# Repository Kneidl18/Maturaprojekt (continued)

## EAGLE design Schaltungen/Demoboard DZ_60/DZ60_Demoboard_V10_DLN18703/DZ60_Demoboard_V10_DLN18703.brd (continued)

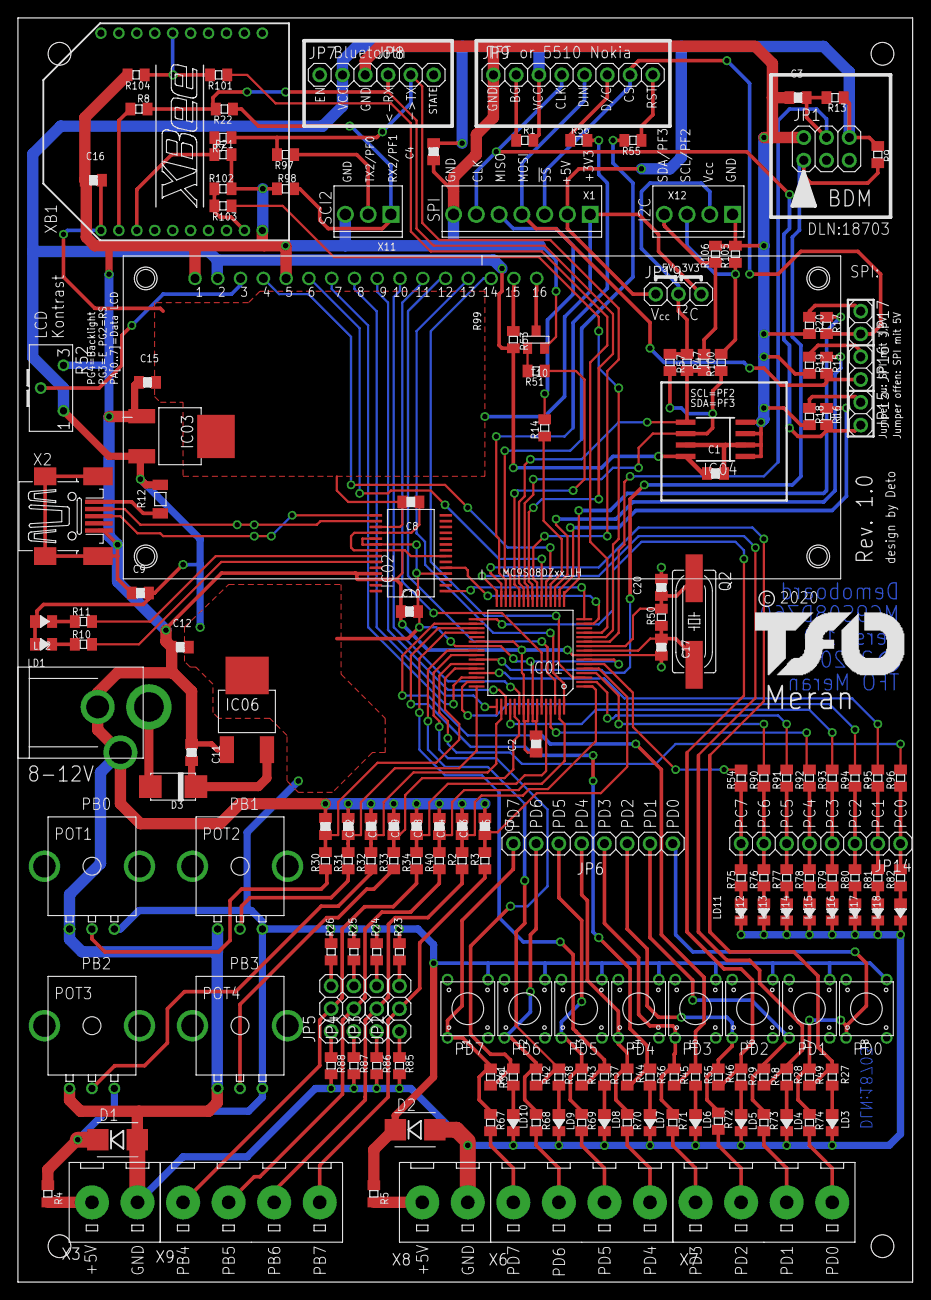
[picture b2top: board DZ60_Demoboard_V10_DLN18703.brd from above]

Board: 2 copper layers, 99.8 x 141.0 mm, 180 parts (0 on the bottom side), 146 nets.

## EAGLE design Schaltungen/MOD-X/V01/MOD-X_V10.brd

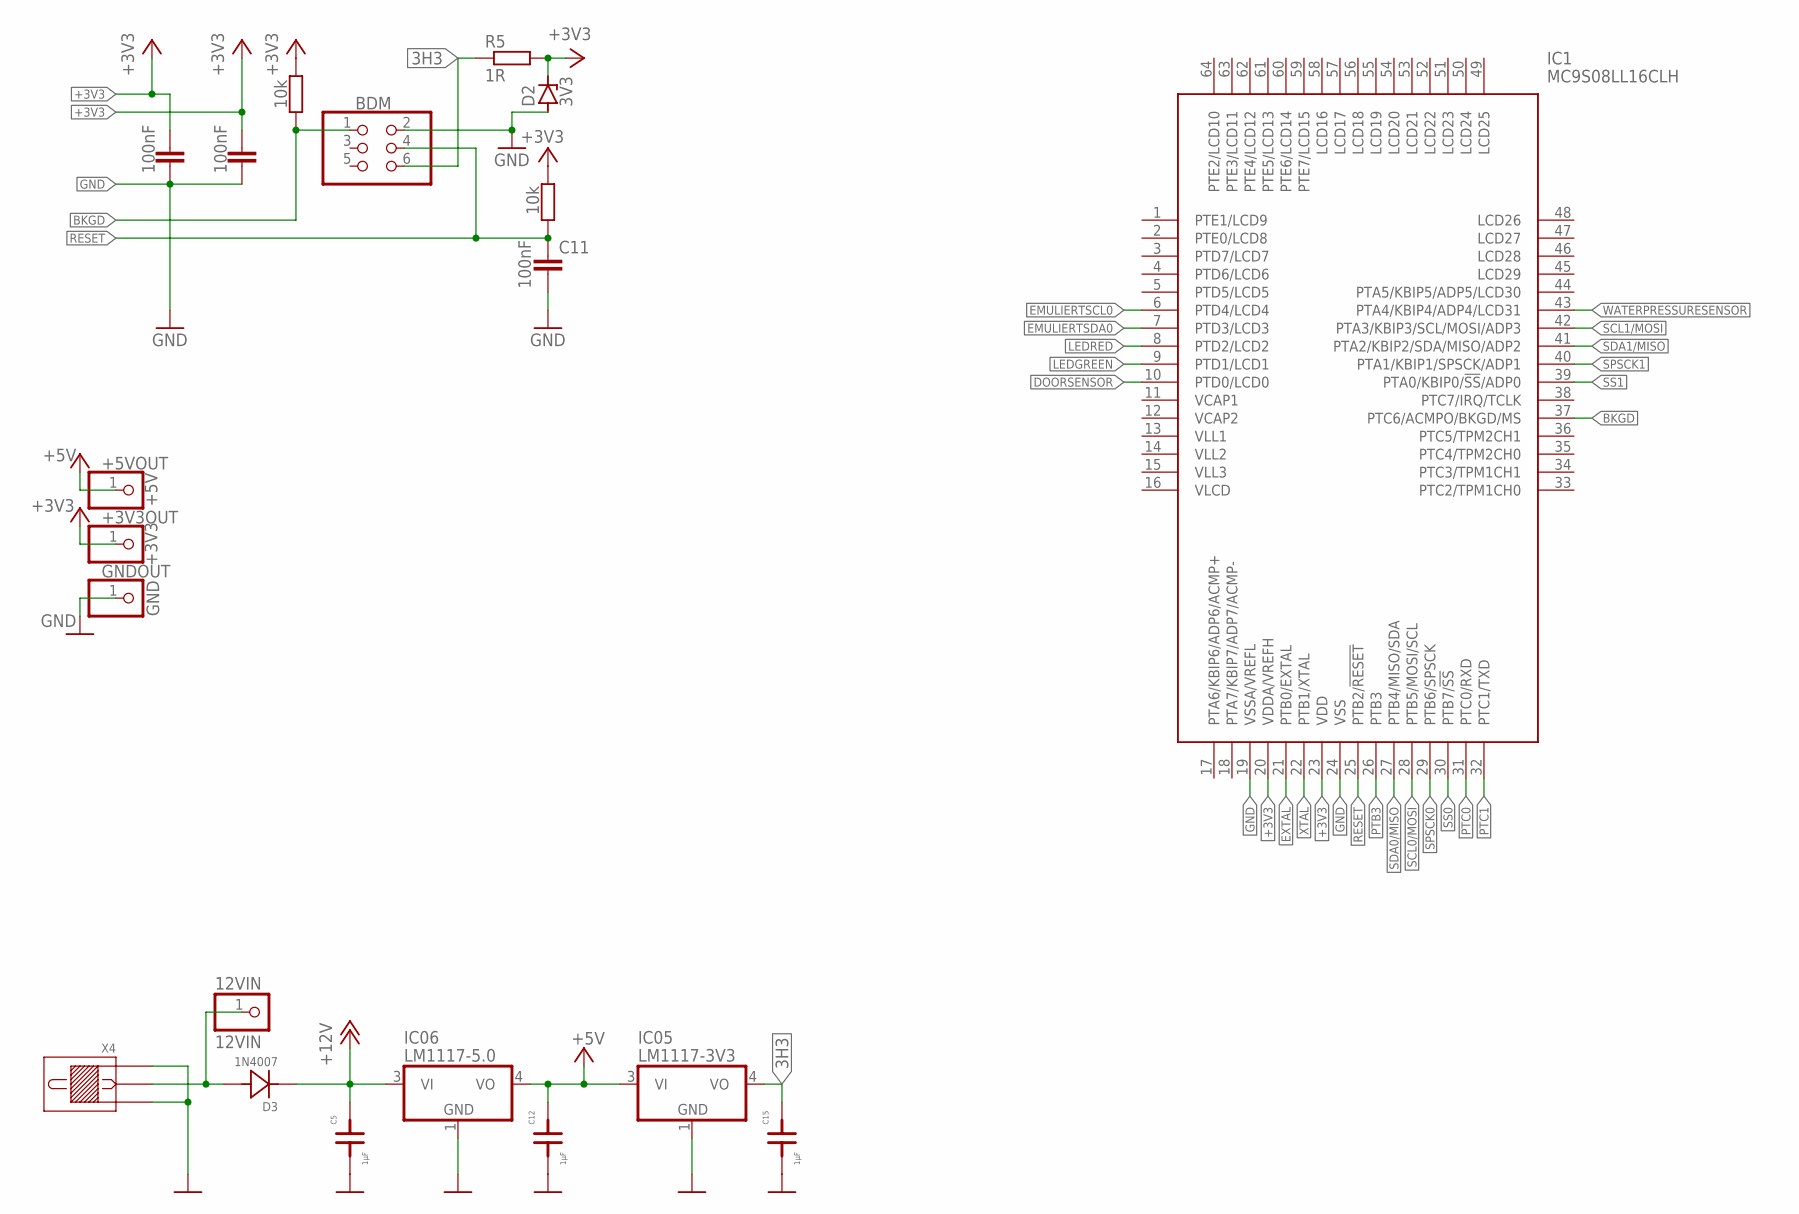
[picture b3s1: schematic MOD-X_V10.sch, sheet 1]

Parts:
12VIN: 12VIN; 1X01
+3V3OUT: +3V3; 1X01
+5VOUT: +5V; 1X01
BDM: PINHD-2X3; 2X03
C5, C12, C15: 1µF; 0805F
C9, C10, C11: 100nF; C0805
D2: 3V3; SOD80C
D3: 1N4007; MELF_B
GNDOUT: GND; 1X01
IC1: MC9S08LL16CLH; QFP50P1200X1200X160-64N
IC05: LM1117-3V3; DPAK
IC06: LM1117-5.0; DPAK
R5: 1R; R0805
R16, R17: 10k; R0805
X4: SPP

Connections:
3H3: BDM.6, C15.2, IC05.4 (VO), R5.1
+3V3: +3V3OUT.1, C9.1, C10.1, D2.C, IC1.20 (VDDA/VREFH), IC1.23 (VDD), R5.2, R16.2, R17.2; also elsewhere on the board
+5V: +5VOUT.1, C12.2, IC05.3 (VI), IC06.4 (VO); also elsewhere on the board
+12V: C5.2, D3.K, IC06.3 (VI); also elsewhere on the board
BKGD: BDM.1, IC1.37 (PTC6/ACMPO/BKGD/MS), R16.1
DOORSENSOR: IC1.10 (PTD0/LCD0); also elsewhere on the board
EMULIERTSCL0: IC1.6 (PTD4/LCD4); also elsewhere on the board
EMULIERTSDA0: IC1.7 (PTD3/LCD3); also elsewhere on the board
EXTAL: IC1.21 (PTB0/EXTAL); also elsewhere on the board
GND: BDM.2, C5.1, C9.2, C10.2, C11.2, C12.1, C15.1, D2.A, GNDOUT.1, IC1.19 (VSSA/VREFL), IC1.24 (VSS), IC05.1 (GND), IC06.1 (GND), X4.1, X4.3; also elsewhere on the board
LEDGREEN: IC1.9 (PTD1/LCD1); also elsewhere on the board
LEDRED: IC1.8 (PTD2/LCD2); also elsewhere on the board
unnamed: 12VIN.1, D3.A, X4.2
PTB3: IC1.26 (PTB3); also elsewhere on the board
PTC0: IC1.31 (PTC0/RXD); also elsewhere on the board
PTC1: IC1.32 (PTC1/TXD); also elsewhere on the board
RESET: BDM.4, C11.1, IC1.25 (PTB2/!RESET), R17.1
SCL0/MOSI: IC1.28 (PTB5/MOSI/SCL); also elsewhere on the board
SCL1/MOSI: IC1.42 (PTA3/KBIP3/SCL/MOSI/ADP3)
SDA0/MISO: IC1.27 (PTB4/MISO/SDA); also elsewhere on the board
SDA1/MISO: IC1.41 (PTA2/KBIP2/SDA/MISO/ADP2)
SPSCK0: IC1.29 (PTB6/SPSCK); also elsewhere on the board
SPSCK1: IC1.40 (PTA1/KBIP1/SPSCK/ADP1)
SS0: IC1.30 (PTB7/!SS); also elsewhere on the board
SS1: IC1.39 (PTA0/KBIP0/!SS!/ADP0)
WATERPRESSURESENSOR: IC1.43 (PTA4/KBIP4/ADP4/LCD31); also elsewhere on the board
XTAL: IC1.22 (PTB1/XTAL); also elsewhere on the board

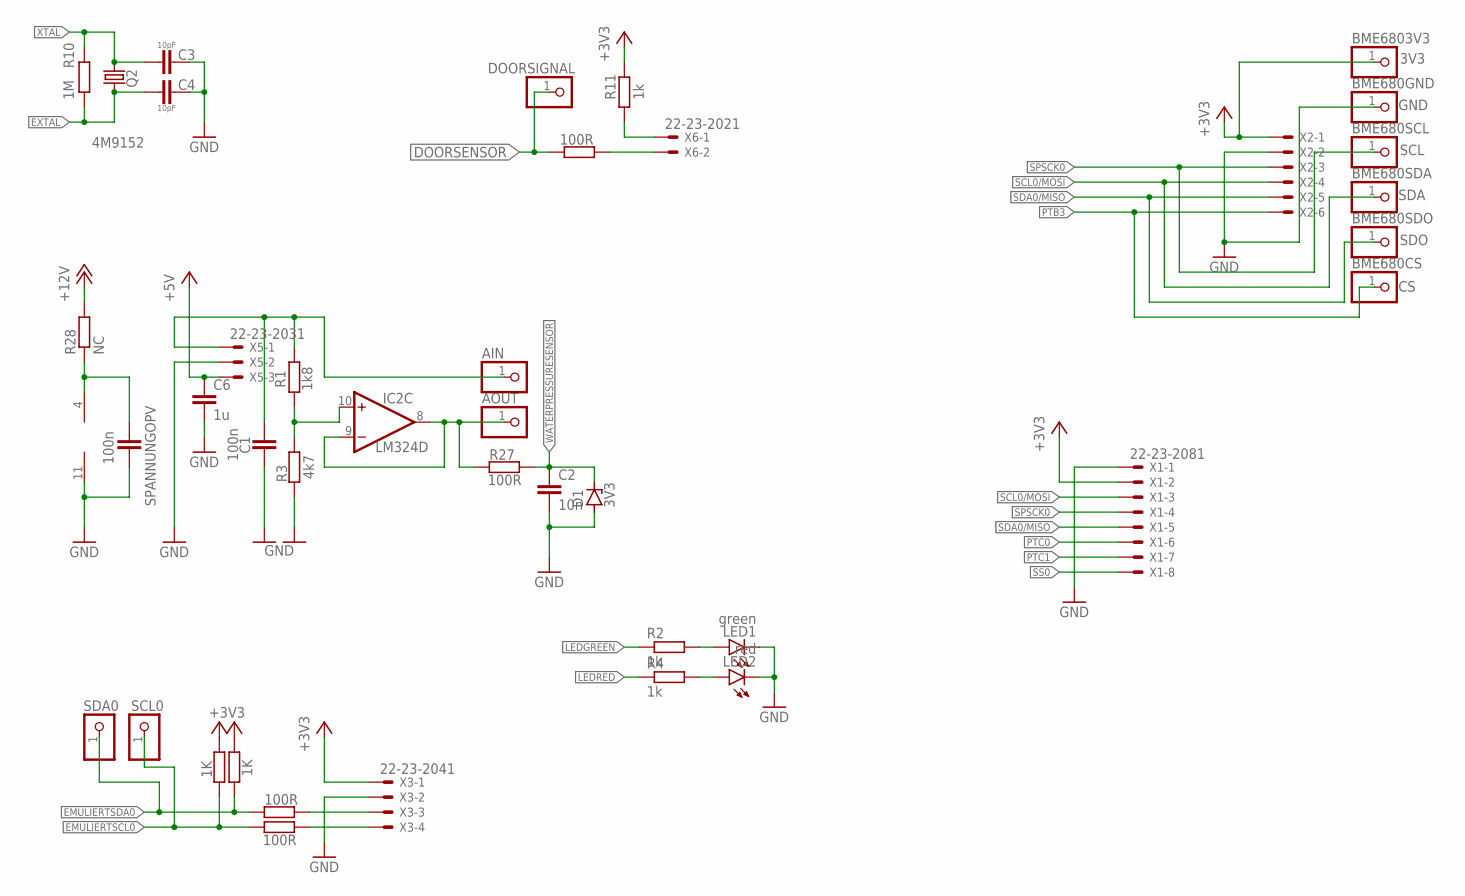
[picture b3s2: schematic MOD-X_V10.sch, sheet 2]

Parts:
AIN: PINHD-1X1; 1X01
AOUT: PINHD-1X1; 1X01
BME680CS: CS; 1X01
BME680GND: GND; 1X01
BME680SCL: SCL; 1X01
BME680SDA: SDA; 1X01
BME680SDO: SDO; 1X01
BME6803V3: 3V3; 1X01
C1: 100n; C0805
C2: 10n; C0805
C3, C4: 10pF; C0805
C6: 1u; C0805
D1: 3V3; SOD80C
DOORSIGNAL: PINHD-1X1; 1X01
IC2: LM324D; SO14
LED1: green; CHIP-LED0805
LED2: red; CHIP-LED0805
Q2: 4M9152; HC49UP
R1: 1k8; R0805
R2, R4, R11: 1k; R0805
R3: 4k7; R0805
R6, R7, R8, R27: 100R; R0805
R9, R18: 1K; R0805
R10: 1M; R0805
R28: NC; R0805
SCL0: PINHD-1X1; 1X01
SDA0: PINHD-1X1; 1X01
SPANNUNGOPV: 100n; C0805
X1: 22-23-2081
X2: 22-23-2061
X3: 22-23-2041
X5: 22-23-2031
X6: 22-23-2021

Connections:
+3V3: BME6803V3.1, R9.2, R11.2, R18.2, X1.2, X2.1, X3.1; also elsewhere on the board
+5V: C6.1, X5.3; also elsewhere on the board
+12V: R28.2; also elsewhere on the board
DOORSENSOR: DOORSIGNAL.1, R6.1; also elsewhere on the board
EMULIERTSCL0: R8.1, R18.1, SCL0.1; also elsewhere on the board
EMULIERTSDA0: R7.1, R9.1, SDA0.1; also elsewhere on the board
EXTAL: C4.1, Q2.1, R10.1; also elsewhere on the board
GND: BME680GND.1, C1.2, C2.2, C3.2, C4.2, C6.2, D1.A, IC2.11 (V-), LED1.C, LED2.C, R3.1, SPANNUNGOPV.2, X1.1, X2.2, X3.2, X5.2; also elsewhere on the board
LEDGREEN: R2.1; also elsewhere on the board
LEDRED: R4.1; also elsewhere on the board
unnamed: IC2.10 (+IN), R1.1, R3.2
unnamed: AIN.1, C1.1, R1.2, X5.1
unnamed: R6.2, X6.2
unnamed: R11.1, X6.1
unnamed: IC2.4 (V+), R28.1, SPANNUNGOPV.1
unnamed: LED1.A, R2.2
unnamed: R8.2, X3.4
unnamed: R7.2, X3.3
unnamed: LED2.A, R4.2
unnamed: AOUT.1, IC2.8 (OUT), IC2.9 (-IN), R27.1
PTB3: BME680CS.1, X2.6; also elsewhere on the board
PTC0: X1.6; also elsewhere on the board
PTC1: X1.7; also elsewhere on the board
SCL0/MOSI: BME680SDA.1, X1.3, X2.4; also elsewhere on the board
SDA0/MISO: BME680SDO.1, X1.5, X2.5; also elsewhere on the board
SPSCK0: BME680SCL.1, X1.4, X2.3; also elsewhere on the board
SS0: X1.8; also elsewhere on the board
WATERPRESSURESENSOR: C2.1, D1.C, R27.2; also elsewhere on the board
XTAL: C3.1, Q2.2, R10.2; also elsewhere on the board

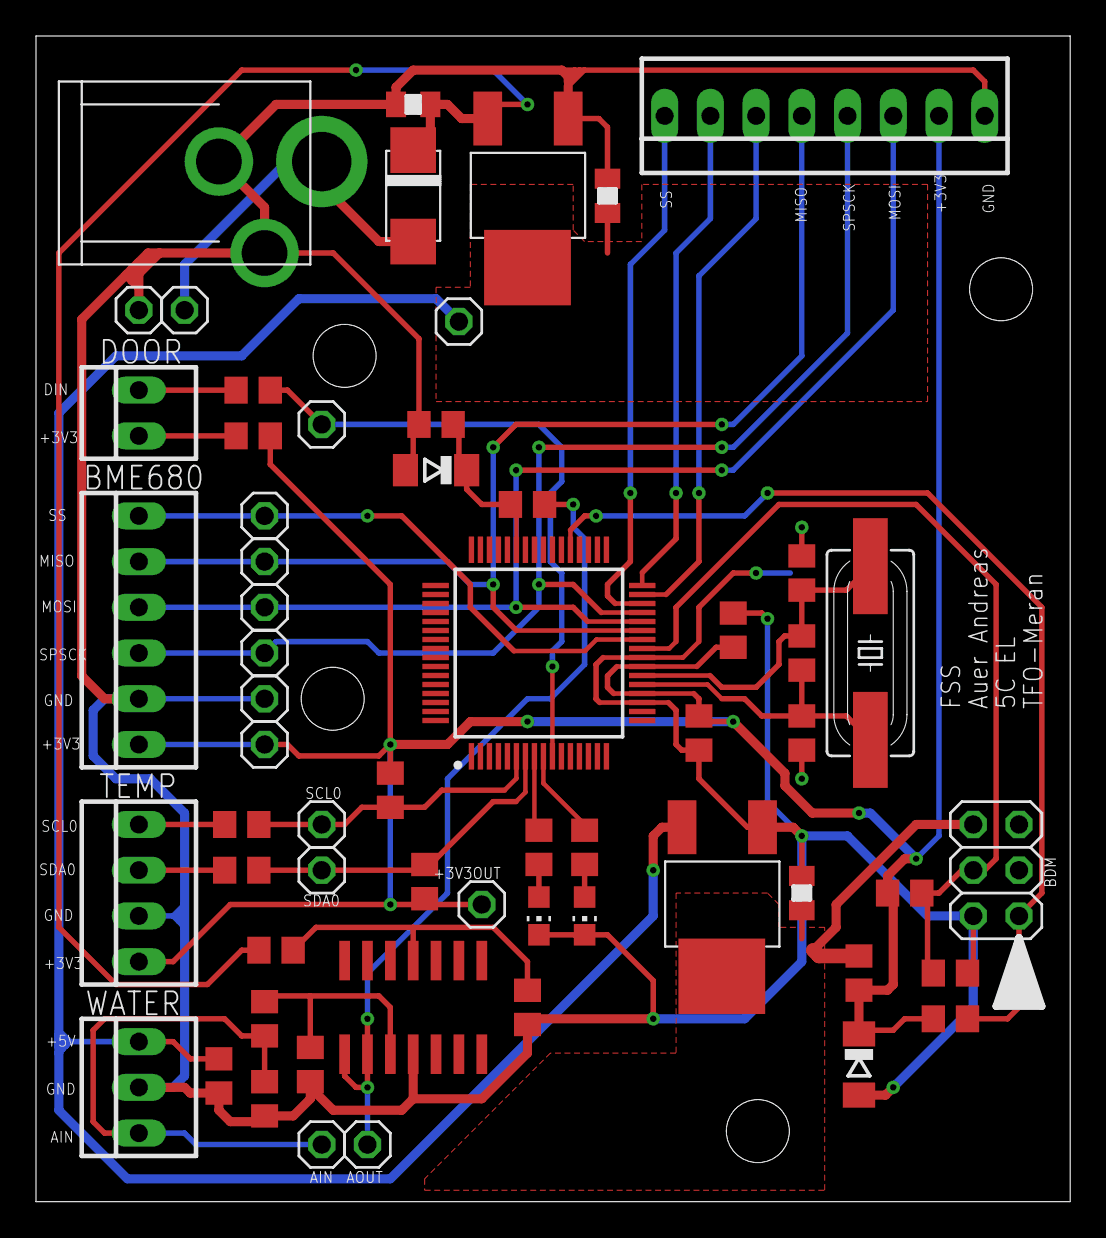
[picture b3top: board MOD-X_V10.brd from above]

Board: 2 copper layers, 57.5 x 64.8 mm, 60 parts (0 on the bottom side), 33 nets.

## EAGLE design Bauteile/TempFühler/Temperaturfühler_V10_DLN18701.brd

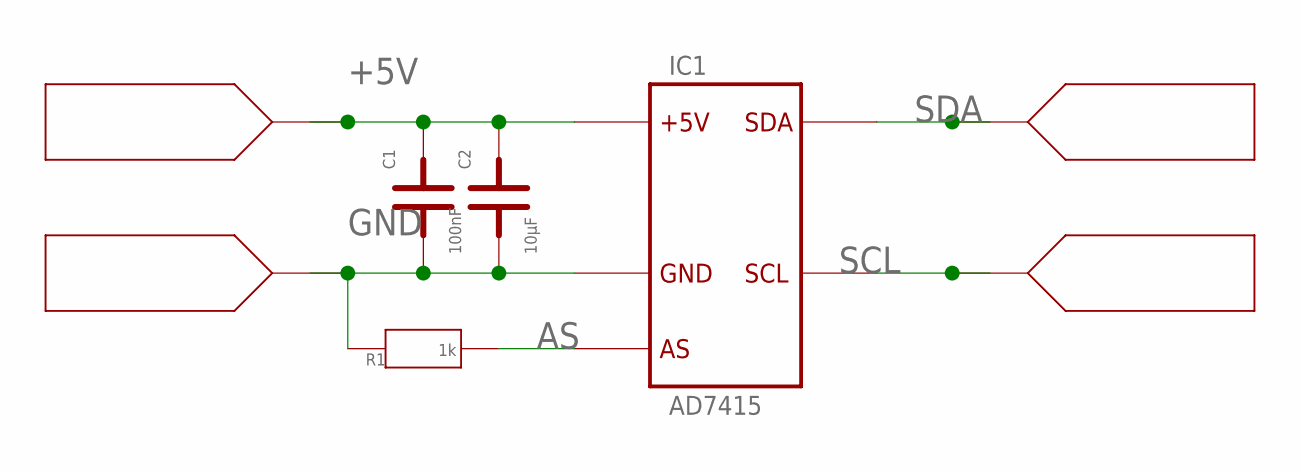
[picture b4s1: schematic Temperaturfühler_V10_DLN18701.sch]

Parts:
C1: 100nF; 0805F
C2: 10µF; 0805F
IC1: AD7415; SOT23-5L
LP1, LP2, LP3, LP4: LP1; LPS1
R1: 1k; 0805

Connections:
+5V: C1.2, C2.2, IC1.3 (+5V), LP3.1
AS: IC1.1 (AS), R1.1
GND: C1.1, C2.1, IC1.2 (GND), LP4.1, R1.2
SCL: IC1.4 (SCL), LP2.1
SDA: IC1.5 (SDA), LP1.1

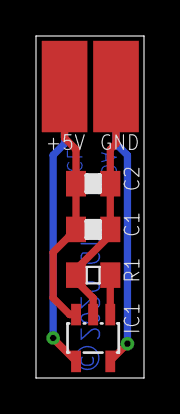
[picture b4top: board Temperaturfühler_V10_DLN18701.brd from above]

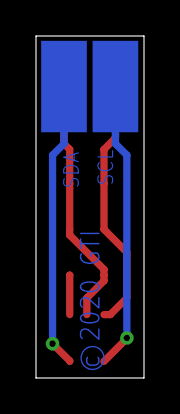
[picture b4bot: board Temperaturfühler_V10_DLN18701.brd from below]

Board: 2 copper layers, 6.0 x 19.0 mm, 8 parts (2 on the bottom side), 5 nets.

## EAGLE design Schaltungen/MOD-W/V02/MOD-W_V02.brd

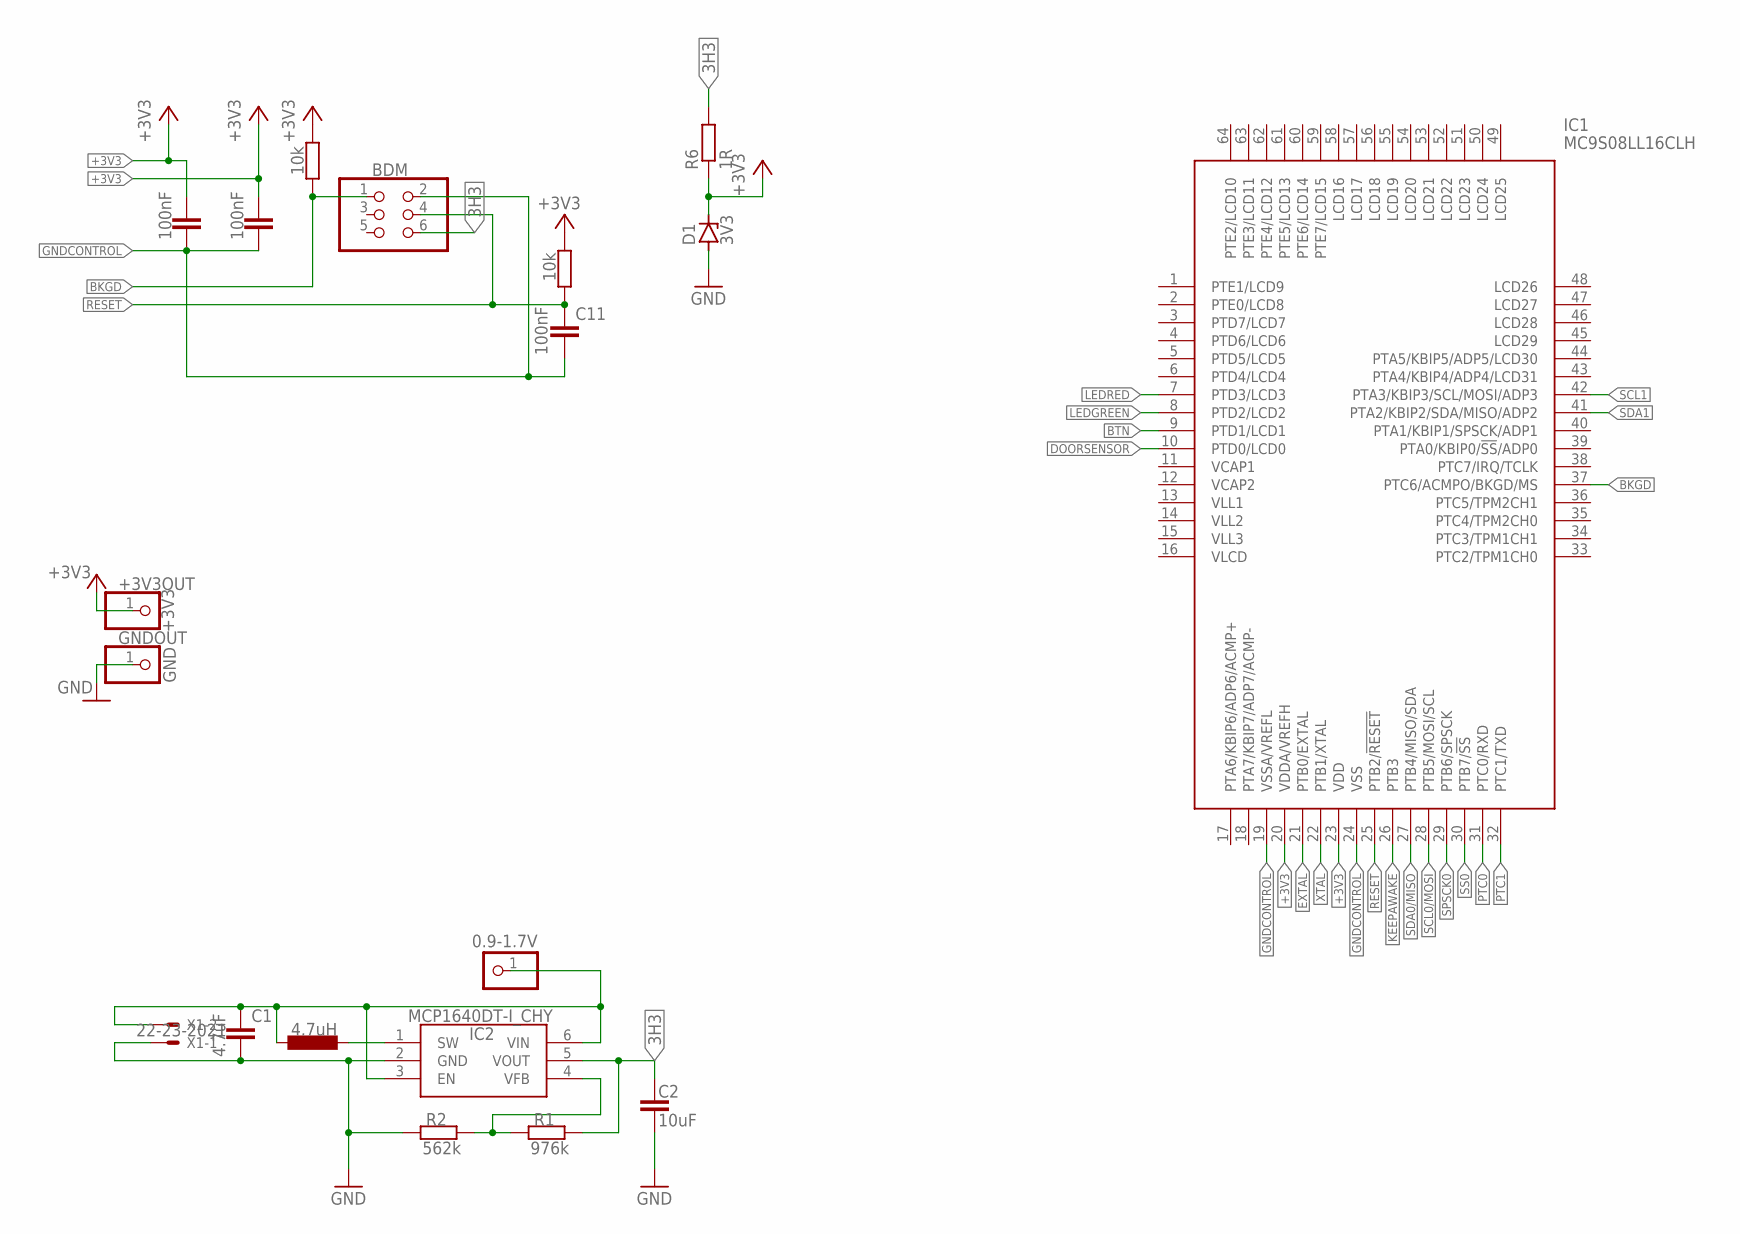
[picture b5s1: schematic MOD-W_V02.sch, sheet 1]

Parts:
+3V3OUT: +3V3; 1X01
BAT: 0.9-1.7V; 1X01
BDM: PINHD-2X3; 2X03
C1: 4.7uF; C0805
C2: 10uF; C0805
C9, C10, C11: 100nF; C0805
D1: 3V3; SOD80C
GNDOUT: GND; 1X01
IC1: MC9S08LL16CLH; QFP50P1200X1200X160-64N
IC2: MCP1640DT-I_CHY; SOT95P270X145-6N
L1: 4.7uH; L2012C
R1: 976k; R0805
R2: 562k; R0805
R6: 1R; R0805
R16, R17: 10k; R0805
X1: 22-23-2021

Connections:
3H3: BDM.6, C2.1, IC2.5 (VOUT), R1.2, R6.2
+3V3: +3V3OUT.1, C9.1, C10.1, D1.C, IC1.20 (VDDA/VREFH), IC1.23 (VDD), R6.1, R16.2, R17.2; also elsewhere on the board
BKGD: BDM.1, IC1.37 (PTC6/ACMPO/BKGD/MS), R16.1
BTN: IC1.9 (PTD1/LCD1)
DOORSENSOR: IC1.10 (PTD0/LCD0); also elsewhere on the board
EXTAL: IC1.21 (PTB0/EXTAL); also elsewhere on the board
GND: C1.2, C2.2, D1.A, GNDOUT.1, IC2.2 (GND), R2.1, X1.1; also elsewhere on the board
GNDCONTROL: BDM.2, C9.2, C10.2, C11.2, IC1.19 (VSSA/VREFL), IC1.24 (VSS); also elsewhere on the board
KEEPAWAKE: IC1.26 (PTB3); also elsewhere on the board
LEDGREEN: IC1.8 (PTD2/LCD2); also elsewhere on the board
LEDRED: IC1.7 (PTD3/LCD3); also elsewhere on the board
unnamed: BAT.1, C1.1, IC2.3 (EN), IC2.6 (VIN), L1.2, X1.2
unnamed: IC2.4 (VFB), R1.1, R2.2
unnamed: IC2.1 (SW), L1.1
PTC0: IC1.31 (PTC0/RXD); also elsewhere on the board
PTC1: IC1.32 (PTC1/TXD); also elsewhere on the board
RESET: BDM.4, C11.1, IC1.25 (PTB2/!RESET), R17.1
SCL0/MOSI: IC1.28 (PTB5/MOSI/SCL); also elsewhere on the board
SCL1: IC1.42 (PTA3/KBIP3/SCL/MOSI/ADP3); also elsewhere on the board
SDA0/MISO: IC1.27 (PTB4/MISO/SDA); also elsewhere on the board
SDA1: IC1.41 (PTA2/KBIP2/SDA/MISO/ADP2); also elsewhere on the board
SPSCK0: IC1.29 (PTB6/SPSCK); also elsewhere on the board
SS0: IC1.30 (PTB7/!SS); also elsewhere on the board
XTAL: IC1.22 (PTB1/XTAL); also elsewhere on the board

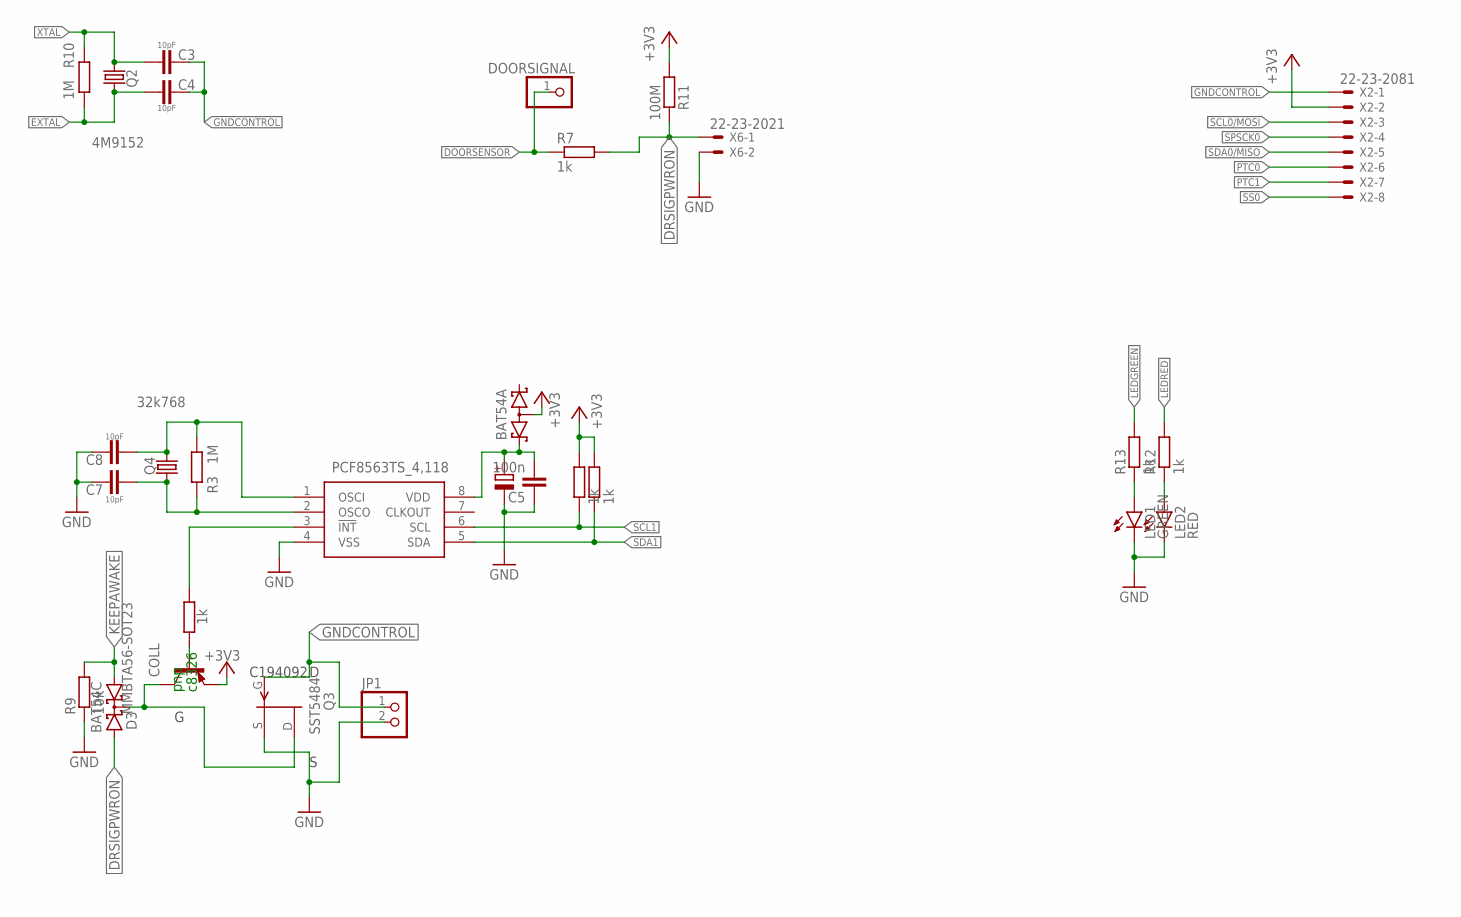
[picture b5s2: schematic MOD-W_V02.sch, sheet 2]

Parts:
C3, C4, C7, C8: 10pF; C0805
C5: 100n; C0805
C6: 100u; PANASONIC_E
D2: BAT54A; SOT23
D3: BAT54C; SOT23
DOORSIGNAL: PINHD-1X1; 1X01
IC3: PCF8563TS_4,118; SOP65P490X110-8N
JP1: PINHD-1X2; 1X02
LED1: GREEN; CHIP-LED0805
LED2: RED; CHIP-LED0805
Q1: MMBTA56-SOT23; SOT23
Q2: 4M9152; HC49UP
Q3: SST5484; SOT23
Q4: 32k768; TC38H
R3, R10: 1M; R0805
R4, R5, R7, R8, R12, R13: 1k; R0805
R9: 10k; R0805
R11: 100M; R0805
X2: 22-23-2081
X6: 22-23-2021

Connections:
+3V3: D2.3 (AA), Q1.2 (E), R4.2, R5.2, R11.1, X2.2; also elsewhere on the board
COLL: D3.3 (CC), Q1.3 (C), Q3.1 (D)
DOORSENSOR: DOORSIGNAL.1, R7.1; also elsewhere on the board
DRSIGPWRON: D3.2 (A2), R7.2, R11.2, X6.1
EXTAL: C4.1, Q2.1, R10.1; also elsewhere on the board
EXTAL1: C8.1, IC3.1 (OSCI), Q4.1, R3.1
GND: C5.1, C6.-, C7.2, C8.2, IC3.4 (VSS), JP1.2, LED1.C, LED2.C, Q3.2 (S), R9.1, X6.2; also elsewhere on the board
GNDCONTROL: C3.2, C4.2, JP1.1, Q3.3 (G), X2.1; also elsewhere on the board
KEEPAWAKE: D3.1 (A1), R9.2; also elsewhere on the board
LEDGREEN: R13.2; also elsewhere on the board
LEDRED: R12.2; also elsewhere on the board
unnamed: IC3.3 (!INT), R8.2
unnamed: LED1.A, R13.1
unnamed: LED2.A, R12.1
unnamed: Q1.1 (B), R8.1
unnamed: C5.2, C6.+, D2.2 (K2), IC3.8 (VDD)
PTC0: X2.6; also elsewhere on the board
PTC1: X2.7; also elsewhere on the board
SCL0/MOSI: X2.3; also elsewhere on the board
SCL1: IC3.6 (SCL), R4.1; also elsewhere on the board
SDA0/MISO: X2.5; also elsewhere on the board
SDA1: IC3.5 (SDA), R5.1; also elsewhere on the board
SPSCK0: X2.4; also elsewhere on the board
SS0: X2.8; also elsewhere on the board
XTAL: C3.1, Q2.2, R10.2; also elsewhere on the board
XTAL1: C7.1, IC3.2 (OSCO), Q4.2, R3.2

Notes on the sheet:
c8326
pnp
C194092

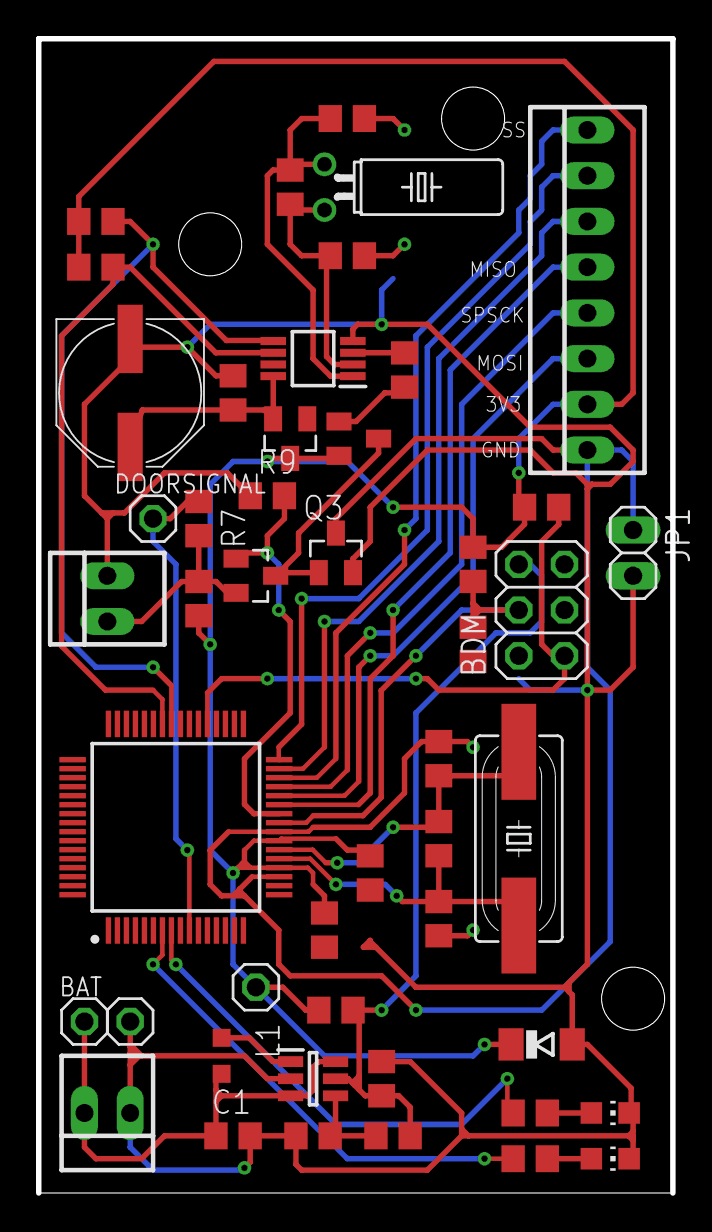
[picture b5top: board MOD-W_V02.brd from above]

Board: 2 copper layers, 35.2 x 64.1 mm, 48 parts (0 on the bottom side), 32 nets.

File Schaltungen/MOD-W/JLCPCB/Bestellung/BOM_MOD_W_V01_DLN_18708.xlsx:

Comment | Designator | Footprint | LCSC Part #（optional）
10pF | C3, C4, C7, C8 | 0805_C | C1785
4,7uF | C1 | 0805_C | C1779
10uF | C2 | 0805_C | C15850
100nF | C5, C9, C10, C11 | 0805_C | C49678
1R | R6 | 0805_R | C25271
1k | R4, R5, R7, R8, R11, R12, R13 | 0805_R | C17513
10k | R16, R17 | 0805_R | C17414
100k | R9 | 0805_R | C25803 | basic but 0603
562k | R2 | 0805_R | C367984 | extended
976k | R1 | 0805_R | C104572 | extended
1M | R3, R10 | 0805_R | C17514
MCP164DT-I_CHY(Spannung) | IC2 | SOT95P270X145-6N | C44365 | extended
 | 36

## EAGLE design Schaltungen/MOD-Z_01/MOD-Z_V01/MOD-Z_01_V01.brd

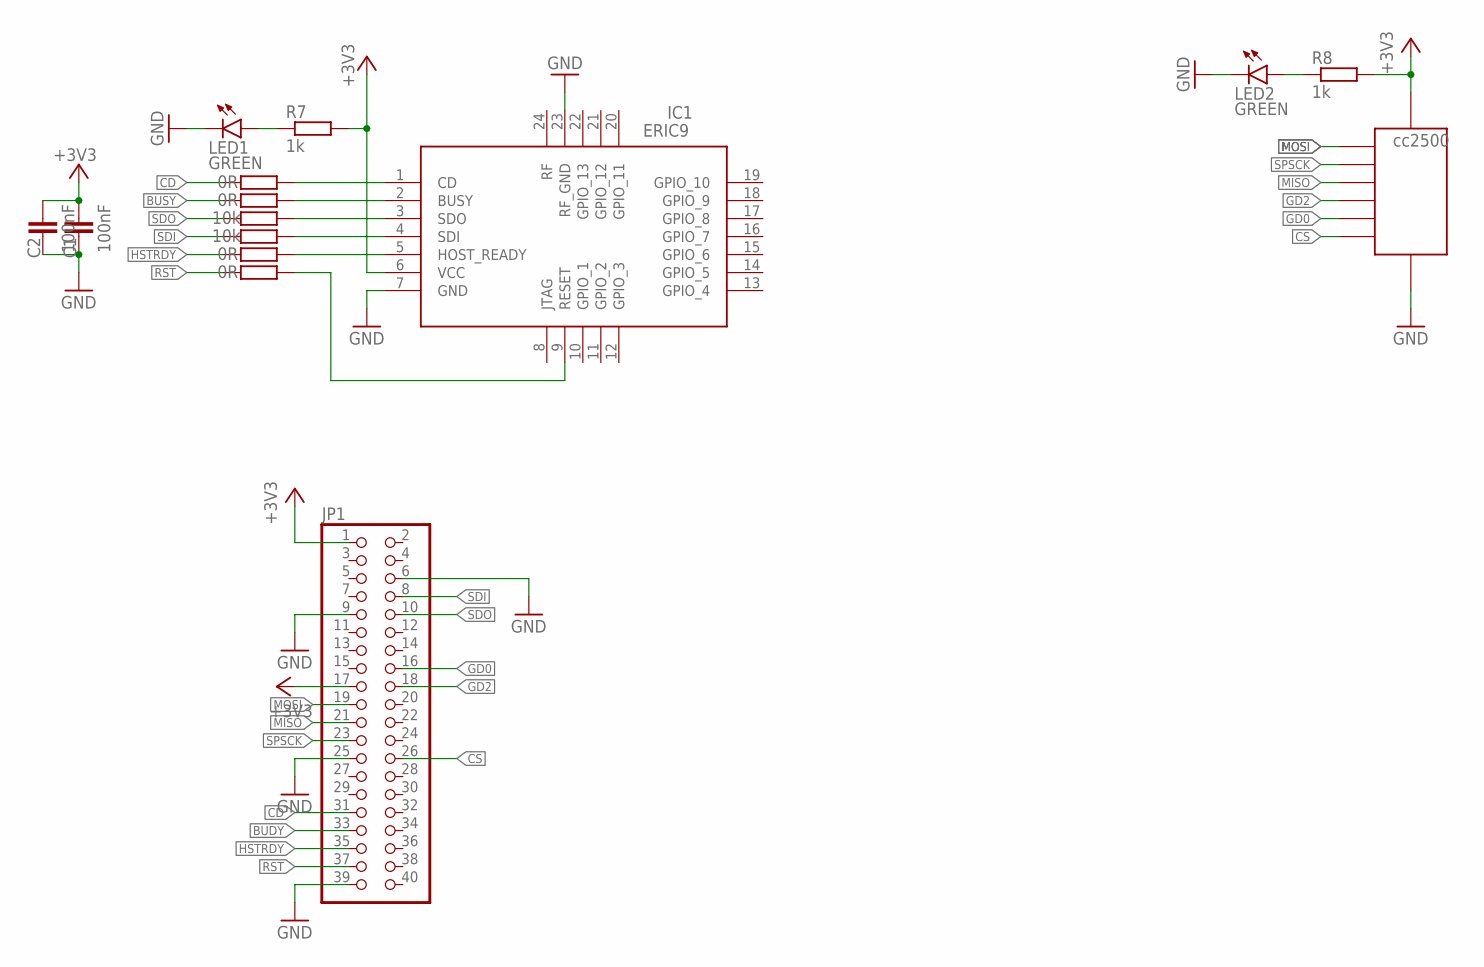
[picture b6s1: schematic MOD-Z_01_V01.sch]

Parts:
C1, C2: 100nF; C0805
IC1: ERIC9
IC2: CC2500
JP1: PINHD-2X20; 2X20
LED1, LED2: GREEN; CHIP-LED0805
R1, R2, R5, R6: 0R; R0805
R3, R4: 10k; R0805
R7, R8: 1k; R0805

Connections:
+3V3: C1.1, C2.1, IC1.6 (VCC), IC2.+3V3, JP1.1, JP1.17, R7.2, R8.2
CD: JP1.31, R1.1
CS: IC2.CS, JP1.26
GD0: IC2.SPSCK, JP1.16
GD2: IC2.MOSI, JP1.18
GND: C1.2, C2.2, IC1.7 (GND), IC1.23 (RF_GND), IC2.GND, JP1.6, JP1.9, JP1.25, JP1.39, LED1.C, LED2.C
HSTRDY: JP1.35, R5.1
MISO: IC2.MISO, JP1.21
MOSI: IC2.GD0, JP1.19
unnamed: LED2.A, R8.1
unnamed: IC1.1 (CD), R1.2
unnamed: IC1.9 (RESET), R6.2
unnamed: IC1.2 (BUSY), R2.2
unnamed: IC1.3 (SDO), R3.2
unnamed: IC1.4 (SDI), R4.2
unnamed: IC1.5 (HOST_READY), R5.2
unnamed: LED1.A, R7.1
RST: JP1.37, R6.1
SDI: JP1.8, R4.1
SDO: JP1.10, R3.1
SPSCK: IC2.GD2, JP1.23

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
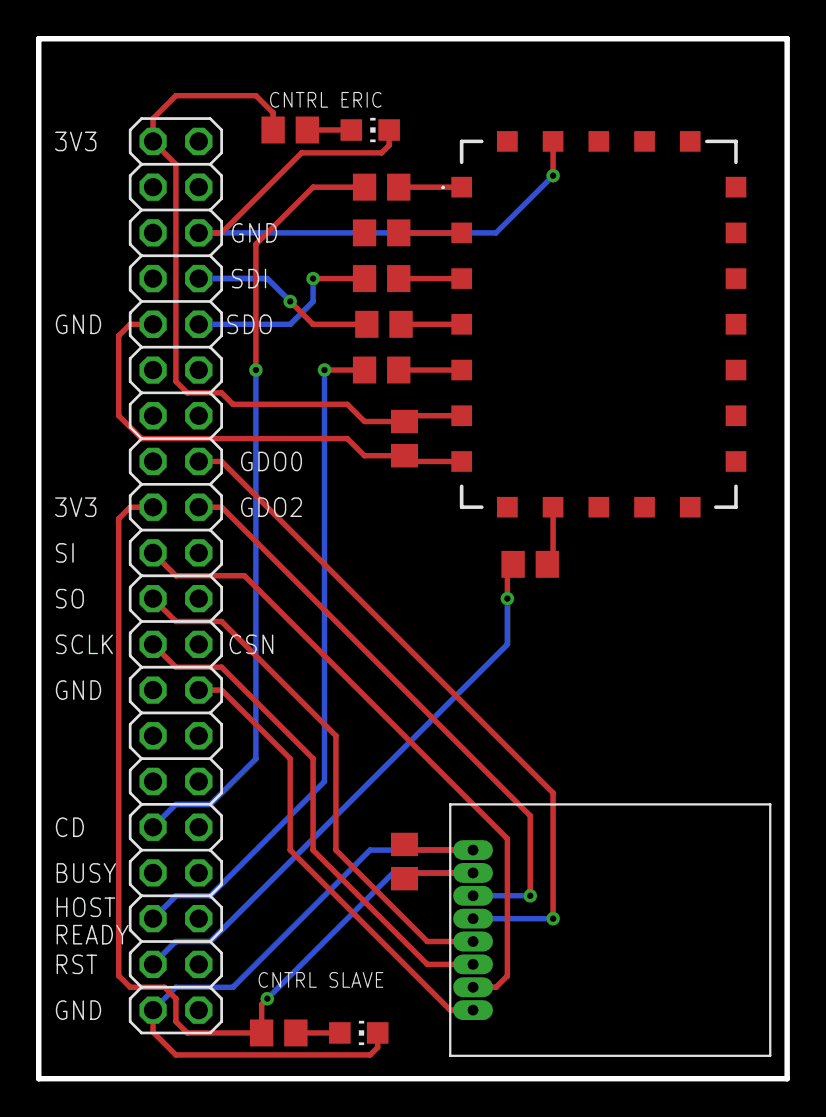
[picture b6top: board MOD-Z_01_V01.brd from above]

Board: 2 copper layers, 41.6 x 57.8 mm, 15 parts (0 on the bottom side), 22 nets.

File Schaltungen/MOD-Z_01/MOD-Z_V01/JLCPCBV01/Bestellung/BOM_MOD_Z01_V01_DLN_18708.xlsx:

Comment | Designator | Footprint | LCSC Part #（optional）
100nF | C1, C2 | 0805_C | C49678
0R | R1, R2, R5, R6 | 0805_R | C17477
1k | R7, R8 | 0805_R | C17513
10k | R3, R4 | 0805_R | C17514
